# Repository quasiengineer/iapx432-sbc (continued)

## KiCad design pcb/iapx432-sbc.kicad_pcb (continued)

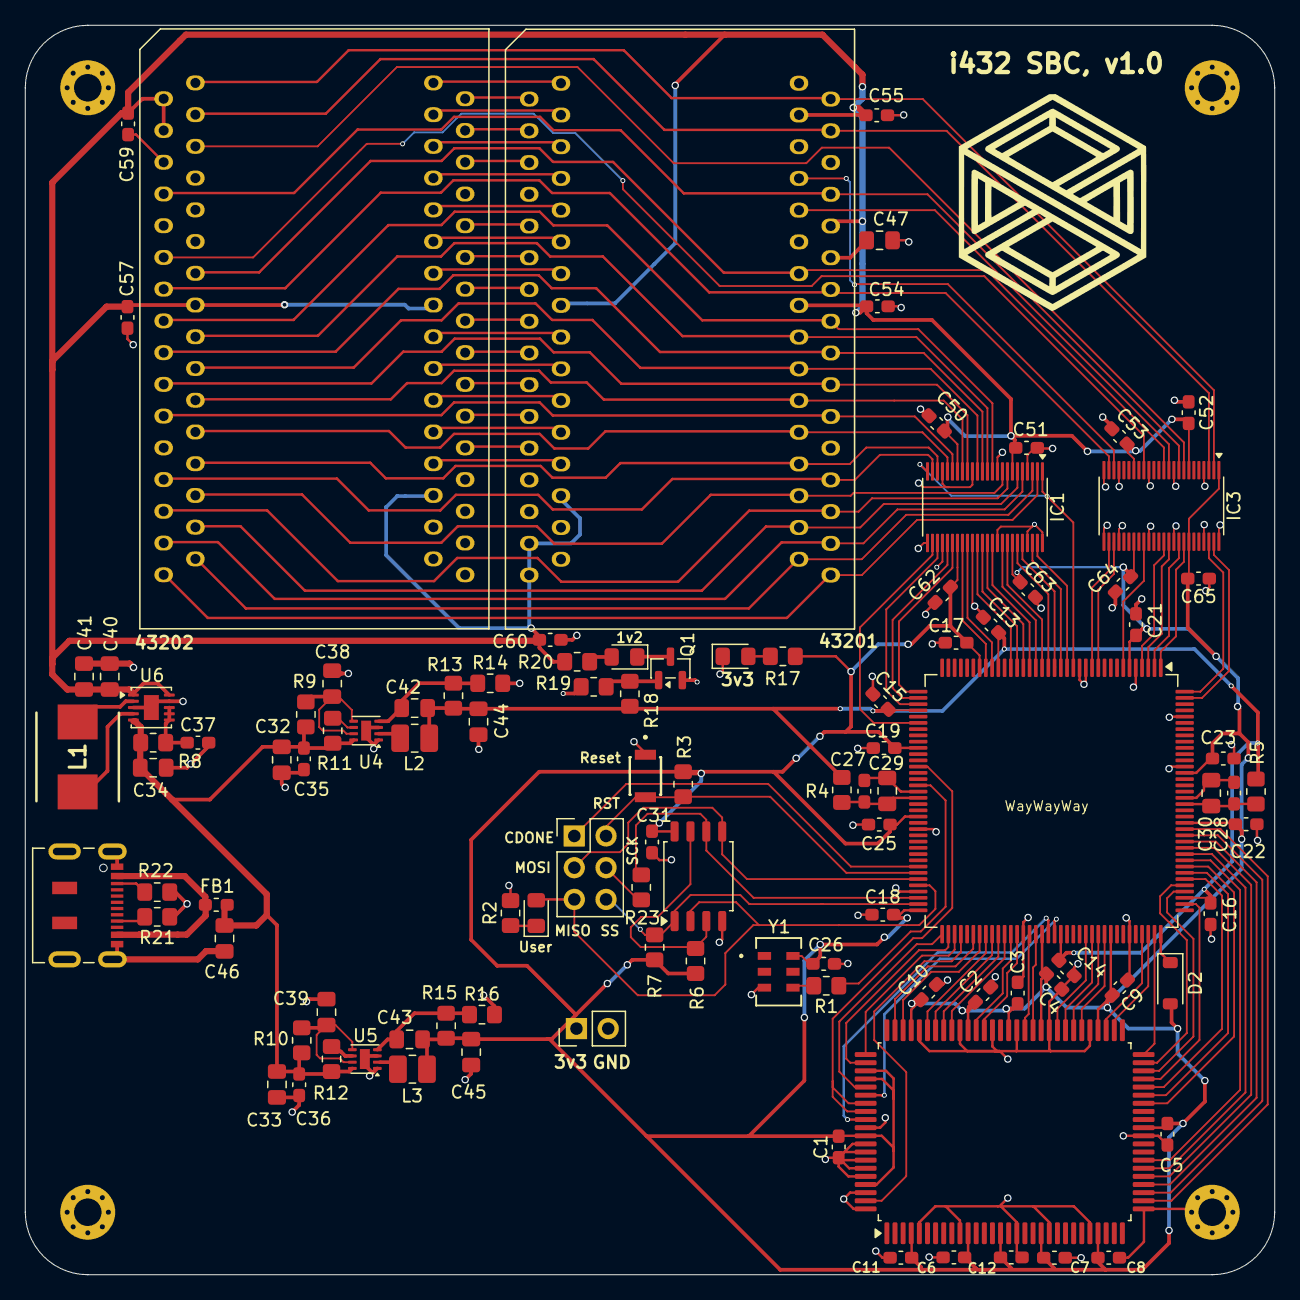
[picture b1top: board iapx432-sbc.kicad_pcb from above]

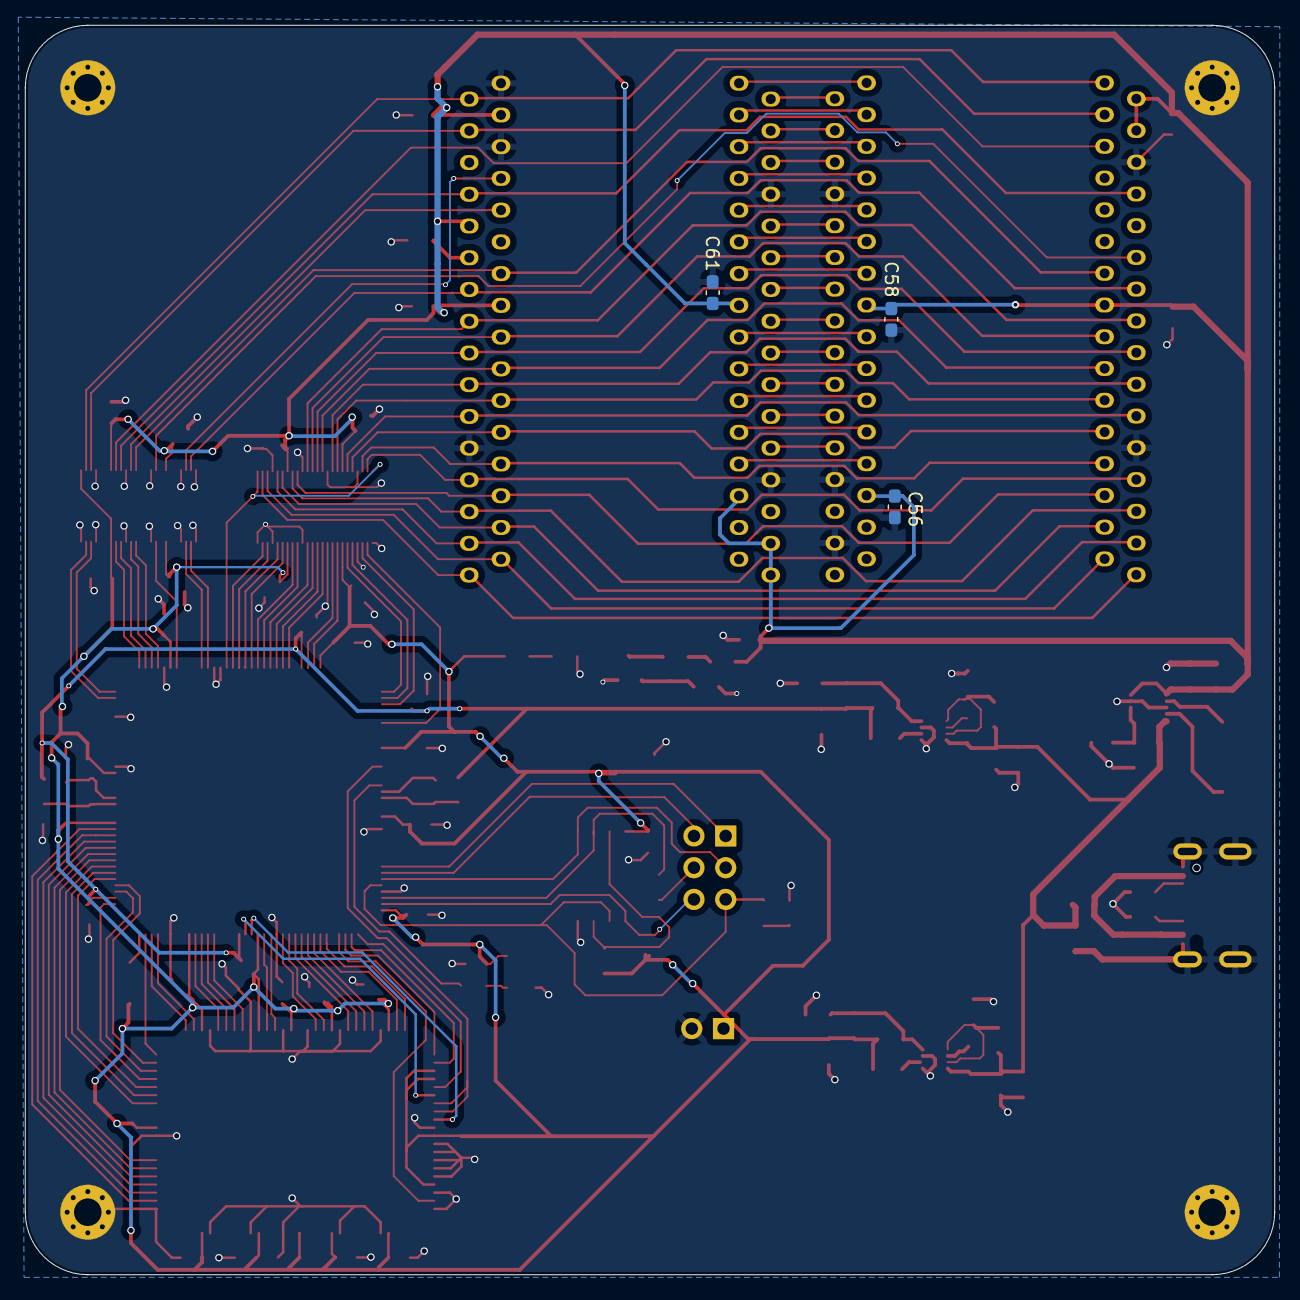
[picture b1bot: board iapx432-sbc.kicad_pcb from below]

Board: 2 copper layers, 100.0 x 100.0 mm, 112 parts (3 on the bottom side), 150 nets.

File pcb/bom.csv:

"Reference","Qty","Value","Mouser Part Number"
"Y1","1","250Mhz","972-XLH536250000000I"
"U1","1","SRAM","870-61LPS12836A5TQL"
"U2","1","ICE40","842-ICE40HX4K-TQ144"
"FB1","1","Ferrite_Bead","81-BLM18BD152SH1D"
"D1","1","Red","710-150080RS75000"
"D3,D4","2","Green","710-150080GS75000"
"J1","1","Type-C","656-DX07S016JA1R1500"
"L1","1","1u5, 5A","652-SRP6530A-1R5M"
"L2,L3","2","0u68, 5.5A","652-SRP2512-R68M"
"J3","1","Power","649-67997-200HLF"
"J2","1","FPGA programming / UART","649-1012938190604BLF"
"SW1","1","FPGA Reset","640-SWT0010015016SSA"
"Q1","1","MMBT3904","637-MMBT3904"
"D2","1","1N5819","621-1N5819HW-F"
"R11,R12,R13,R14,R19","5","100k","603-RT0805DRE07100KL"
"R23","1","470R","603-RT0805BRD07470RL"
"R21,R22","2","5k1","603-RC0805FR-075K1L"
"R2,R18","2","4k7","603-RC0805FR-074K7L"
"R16","1","34k8","603-RC0805FR-0734K8L"
"R17,R20","2","2k2","603-RC0805FR-072K2L"
"R15","1","158k","603-RC0805FR-07158KL"
"R1","1","22R","603-RC0805FR-1322RL"
"C43","1","33p","603-CC805KRNPO9BN330"
"C42","1","22p","603-CC805JRNPO9BN220"
"R9,R10","2","10","603-AF0805FR-0710RL"
"R4,R5,R8","3","100R","603-AC0805FR-13100RL"
"R3,R6,R7","3","10k","603-AA0805FR-0710KL "
"U6","1","TPS63002","595-TPS63002DRCR"
"IC3","1","Control signals","595-LVC16T245DGVRG4"
"IC1","1","Address/data bus","595-LVC16T245DGVRG4"
"U4,U5","2","LX7167ACLD-TR","494-LX7167ACLD-TR"
"U3","1","Bitstream flash","454-W25Q16JVSSIQ"
"C38,C39,C46,C47","4","1u","187-CL21B105KPFNNNE"
"C29,C30,C32,C33,C44,C45","6","22u","187-CL21A226MAYNNNE"
"C34,C40,C41","3","10u","187-CL21A106KQFNNNG"
"C1,C2,C3,C4,C5,C6,C7,C8,C9,C10,C11,C12,C13,C14,C15,C16,C17,C18,C19,C21,C22,C23,C25,C26,C27,C28,C31,C35,C36,C37,C50,C51,C52,C53,C54,C55,C56,C57,C58,C59,C60,C61,C62,C63,C64,C65","46","100n","187-CL10B104KB8NNNC"
"U8","1","43202",""
"U7","1","43201",""
"H1,H2,H3,H4","4","MountingHole_Pad",""

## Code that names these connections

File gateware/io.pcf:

# Control
set_io SRAM_STROBE 73
set_io SRAM_CLK    90
set_io SRAM_OE     91
set_io SRAM_WR     49

# Address bus
set_io SRAM_A[0] 117
set_io SRAM_A[1] 118
set_io SRAM_A[2] 122
set_io SRAM_A[3] 121
set_io SRAM_A[4] 120
set_io SRAM_A[5] 119
set_io SRAM_A[6] 116
set_io SRAM_A[7] 115
set_io SRAM_A[8] 114
set_io SRAM_A[9] 110
set_io SRAM_A[10] 112
set_io SRAM_A[11] 113
set_io SRAM_A[12] 107
set_io SRAM_A[13] 75
set_io SRAM_A[14] 74
set_io SRAM_A[15] 76

# Data bus
set_io SRAM_D[0]  106
set_io SRAM_D[1]  105
set_io SRAM_D[2]  99
set_io SRAM_D[3]  98
set_io SRAM_D[4]  97
set_io SRAM_D[5]  96
set_io SRAM_D[6]  88
set_io SRAM_D[7]  87
set_io SRAM_D[8]  85
set_io SRAM_D[9]  84
set_io SRAM_D[10] 83
set_io SRAM_D[11] 82
set_io SRAM_D[12] 81
set_io SRAM_D[13] 80
set_io SRAM_D[14] 79
set_io SRAM_D[15] 78

# Clock / reset / control
set_io PCLK  1
set_io CLR   2
set_io INIT  3
set_io ICS   4
set_io BOUT  7
set_io FATAL 11
set_io PRQ   12

# Address / control/data (ACD bus)
set_io ACD_DIRECTION 15
set_io ACD[0]  16
set_io ACD[1]  17
set_io ACD[2]  18
set_io ACD[3]  19
set_io ACD[4]  20
set_io ACD[5]  21
set_io ACD[6]  42
set_io ACD[7]  39
set_io ACD[8]  38
set_io ACD[9]  37
set_io ACD[10] 29
set_io ACD[11] 28
set_io ACD[12] 25
set_io ACD[13] 24
set_io ACD[14] 23
set_io ACD[15] 22

set_io CLKA 143
set_io CLKB 144
set_io CLK_250 52

set_io UART_RX 70
set_io UART_TX 67
set_io LED 68

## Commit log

2026-02-10 initial
2026-02-10 bom fmt
2026-02-10 more compact BOM
2026-02-10 SRAM would work at 125Mhz
2026-02-11 adopt UART interface to 16-bit words
2026-02-12 support GDP reads from SRAM
2026-02-12 add bootstrapper that prepares image and runs GDP
2026-02-12 create storage descriptor for root object table
2026-02-12 support GDP write to SRAM
2026-02-13 image builder builds object table directory and processor object table
2026-02-14 add local communication segment
2026-02-14 support multi-word writes
2026-02-17 build delay port and delay carrier objects + support 1-byte writes + fix local comm segment + QoL changes
2026-02-17 build processor carrier object
2026-02-17 allow to "send" different IPCs
2026-02-17 build skeleton of process object
2026-02-18 build process context object
2026-02-18 build domain and instruction objects
2026-02-28 i432 program to write interconnect register
2026-03-04 i432 hello world
2026-03-25 i432 program to compute pi digits
